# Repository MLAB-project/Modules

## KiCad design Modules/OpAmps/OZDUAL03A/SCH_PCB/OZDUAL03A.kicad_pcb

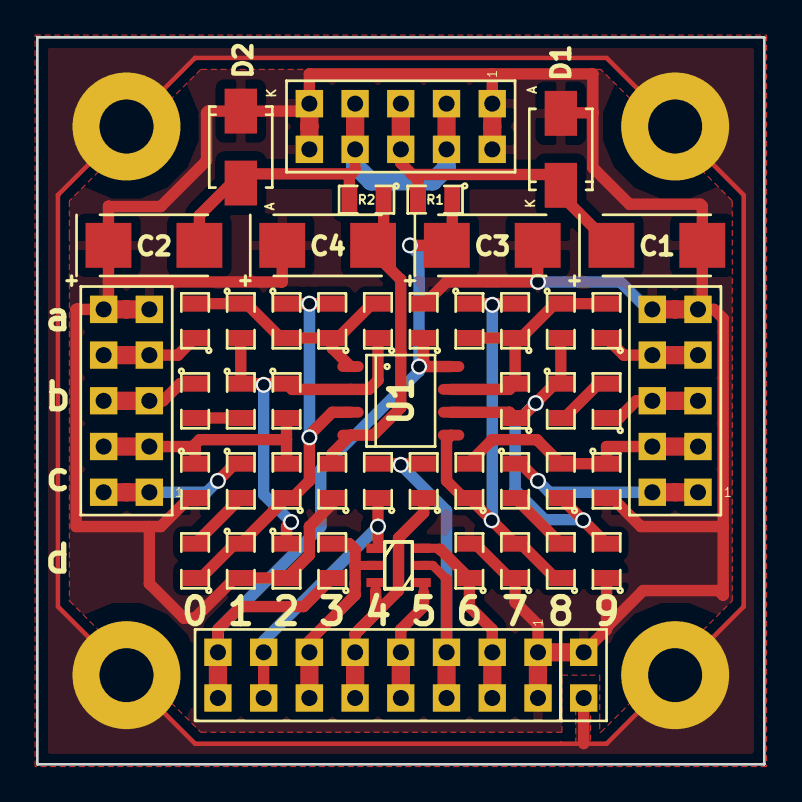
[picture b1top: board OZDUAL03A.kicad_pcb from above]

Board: 2 copper layers, 40.4 x 40.4 mm, 55 parts (0 on the bottom side), 30 nets.

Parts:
C1, C2, C3, C4: 47u; TantalC_SizeC_Reflow
D1, D2: M4; Diode-SMA_Standard
J1: JUMP2_2x1; Straight_2x01
J2: POWER; Straight_2x05
J3: OPAMPA; Straight_2x05
J4: OPAMPB; Straight_2x05
J5: SOT23-6; Straight_2x08
M1, M2, M3, M4: HOLE; MountingHole_3mm
Q1: BC846; SOT-23-3
R1, R2: R; SMD-0805
U1: OZ; SO-8
U2: MAX6066; SOT-23-3
U3: ANALOG SWITCH; SOT-23-6
a0, a2, a4, a6, a9: C; SMD-0805
a1, a3, a7, a8: R; SMD-0805
a5: 100nF; SMD-0805
b0, b7, b9: C; SMD-0805
b1, b2, b8: R; SMD-0805
c0, c1, c4, c5, c7, c9: C; SMD-0805
c2, c6, c8: R; SMD-0805
c3: 100nF; SMD-0805
d0, d1, d2, d3, d6, d7, d8, d9: R; SMD-0805

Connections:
/1: J5.13, J5.14, U2.1, U3.1, c4.1
/2: J5.11, J5.12, Q1.3, U3.2, d3.2
/3: J5.9, J5.10, U2.2, U3.3, c5.1
/4: J5.7, J5.8, Q1.1, U3.4
/5: J5.5, J5.6, U2.3, U3.5, c4.2, c5.2
/6: J5.3, J5.4, Q1.2, U3.6, d6.1
/INA+: J3.1, J3.2, c1.1
/INA-: J3.5, J3.6, b0.1
/INB+: J4.1, J4.2, c7.1
/INB-: J4.5, J4.6, b9.1
/OUTA: J3.7, J3.8, a0.1
/OUTB: J4.7, J4.8, a9.1
/VIN+: C1.1, D1.1, J2.5, J2.6, R1.2
/VIN-: C2.2, D2.2, J2.3, J2.4, J2.7, J2.8, R2.2
/VREFA: J3.3, J3.4, b2.2, c0.1, c2.2
/VREFB: J4.3, J4.4, c6.2, c8.2, c9.1
GND: J1.2, M1.1, M2.1, M3.1, M4.1
GNDA: C1.2, C2.1, C3.2, C4.1, D1.2, D2.1, J1.1, J2.1, J2.2, J2.9, J2.10, J3.9, J3.10, J4.9, J4.10, J5.1, J5.2, a5.2, c0.2, c3.1, c9.2, d1.2, d2.2, d6.2, d7.1, d9.1
unnamed: U1.1, a0.2, a1.1, a2.2, a3.1, a4.2
unnamed: U1.2, a1.2, a4.1, b1.1, b2.1, d2.1
unnamed: U1.3, a2.1, a3.2, c2.1, d0.1, d1.1
unnamed: U1.5, a6.1, a7.2, c6.1, d7.2, d8.1
unnamed: U1.6, a8.2, b7.1, b8.1, c8.1, d9.2
unnamed: U1.7, a6.2, a7.1, a8.1, a9.2, b7.2
unnamed: b0.2, b1.2
unnamed: b8.2, b9.2
unnamed: c1.2, d0.2
unnamed: c7.2, d8.2
VCC: C3.1, J5.15, J5.16, R1.1, U1.8, a5.1, d3.1
VSS: C4.2, R2.1, U1.4, c3.2

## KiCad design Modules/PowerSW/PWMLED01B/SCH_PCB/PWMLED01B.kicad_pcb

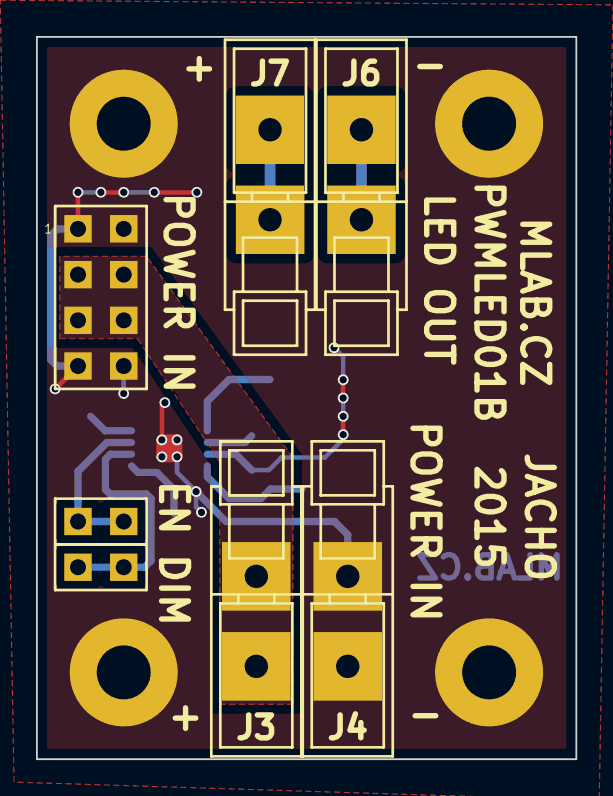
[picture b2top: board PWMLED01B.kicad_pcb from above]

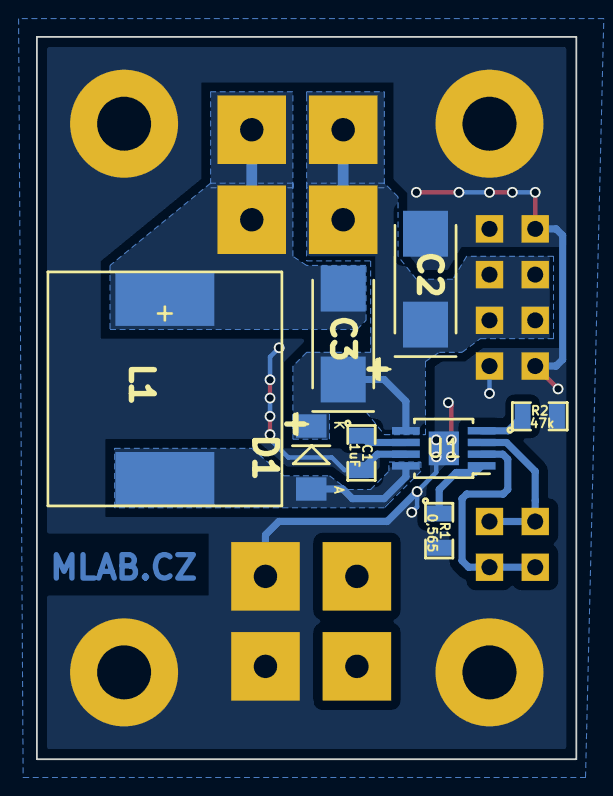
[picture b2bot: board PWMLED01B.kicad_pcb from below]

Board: 2 copper layers, 30.0 x 40.1 mm, 19 parts (8 on the bottom side), 9 nets.

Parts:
C1: 1uF; SMD-0805
C2, C3: 4,7uF; TantalC_SizeC_Reflow
D1: TMMBAT48; Diode-MiniMELF_Standard
J1, J2: JUMP_2x1; Straight_1x02
J3, J4, J6, J7: WAGO256
J5: JUMP_4X2; Straight_2x04
L1: DE1207-22 (22uH); DE1205-10
P1, P2, P3, P4: M3; MountingHole_3mm
R1: 0,565; SMD-0805
R2: 47k; SMD-0805
U1: LM3407; MSOP-8-1EP_3x3mm_Pitch0.65mm

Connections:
/+LED: C2.1, C3.1, D1.2, J3.1, J5.3, J5.4, J5.5, J5.6, J7.1, U1.5
/-LED: C3.2, J6.1, L1.1
/DIM: J1.1, J1.2, U1.2
/EN: J2.1, J2.2, U1.3
GND: C1.2, C2.2, J4.1, J5.1, J5.2, J5.7, J5.8, P1.1, P2.1, P3.1, P4.1, R1.2, R2.2, U1.7, U1.9
unnamed: C1.1, U1.6
unnamed: D1.1, L1.2, U1.8
unnamed: R1.1, U1.1
unnamed: R2.1, U1.4

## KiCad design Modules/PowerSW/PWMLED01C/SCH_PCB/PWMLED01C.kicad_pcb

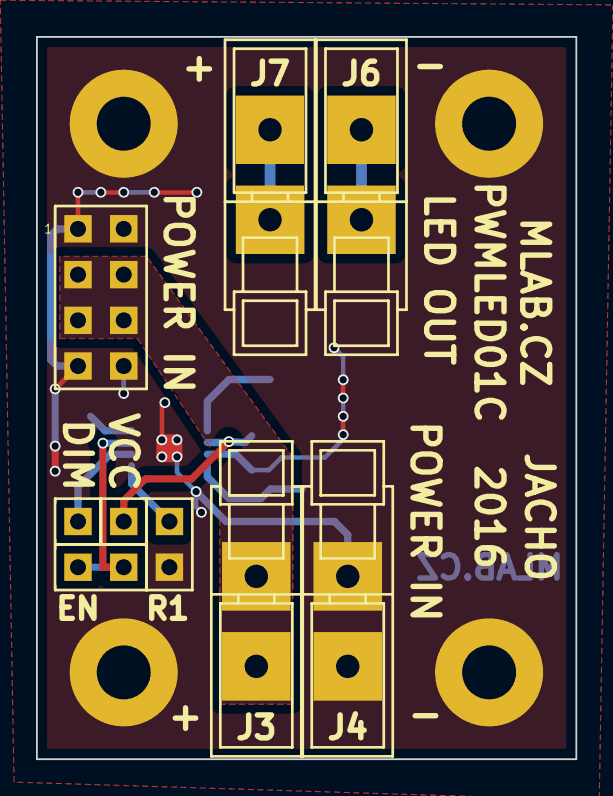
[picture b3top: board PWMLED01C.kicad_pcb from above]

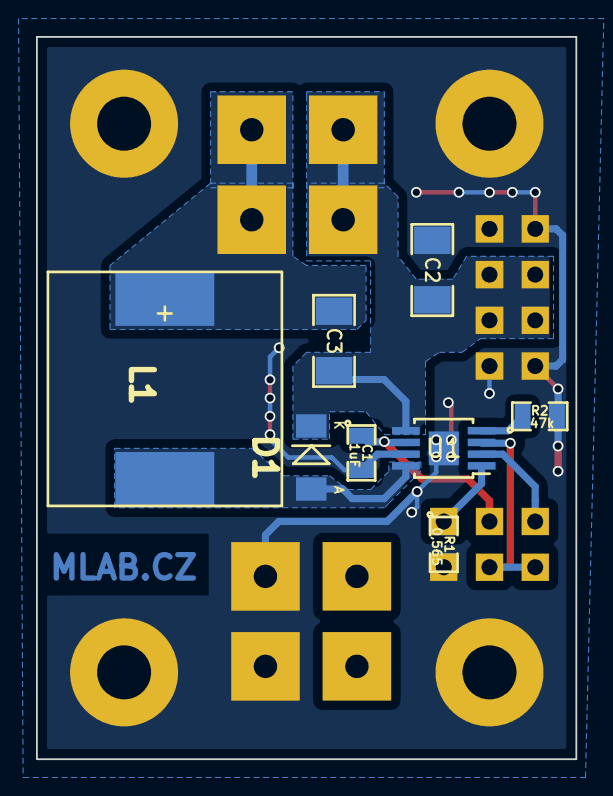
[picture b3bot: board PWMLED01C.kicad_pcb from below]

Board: 2 copper layers, 30.0 x 40.1 mm, 21 parts (8 on the bottom side), 9 nets.

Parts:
C1: 1uF; SMD-0805
C2, C3: 4,7uF/50V; SMD-1206
D1: TMMBAT48; Diode-MiniMELF_Standard
J1: CONN1_2; Straight_1x02
J2: JUMP_2x1; Straight_1x02
J3, J4, J6, J7: WAGO256
J5: JUMP_4X2; Straight_2x04
J8, J9: CONN1_1; Straight_1x01
L1: DE1207-22 (22uH); DE1205-10
P1, P2, P3, P4: M3; MountingHole_3mm
R1: 0,565; SMD-0805
R2: 47k; SMD-0805
U1: LM3407; MSOP-8-1EP_3x3mm_Pitch0.65mm

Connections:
/+LED: C2.1, C3.2, D1.2, J3.1, J5.3, J5.4, J5.5, J5.6, J7.1, U1.5
/-LED: C3.1, J6.1, L1.1
/DIM: J9.1, U1.2
/EN: J2.1, J2.2, U1.3
/Vcc: C1.1, J8.1, U1.6
GND: C1.2, C2.2, J1.1, J4.1, J5.1, J5.2, J5.7, J5.8, P1.1, P2.1, P3.1, P4.1, R1.2, R2.2, U1.7, U1.9
unnamed: D1.1, L1.2, U1.8
unnamed: J1.2, R1.1, U1.1
unnamed: R2.1, U1.4

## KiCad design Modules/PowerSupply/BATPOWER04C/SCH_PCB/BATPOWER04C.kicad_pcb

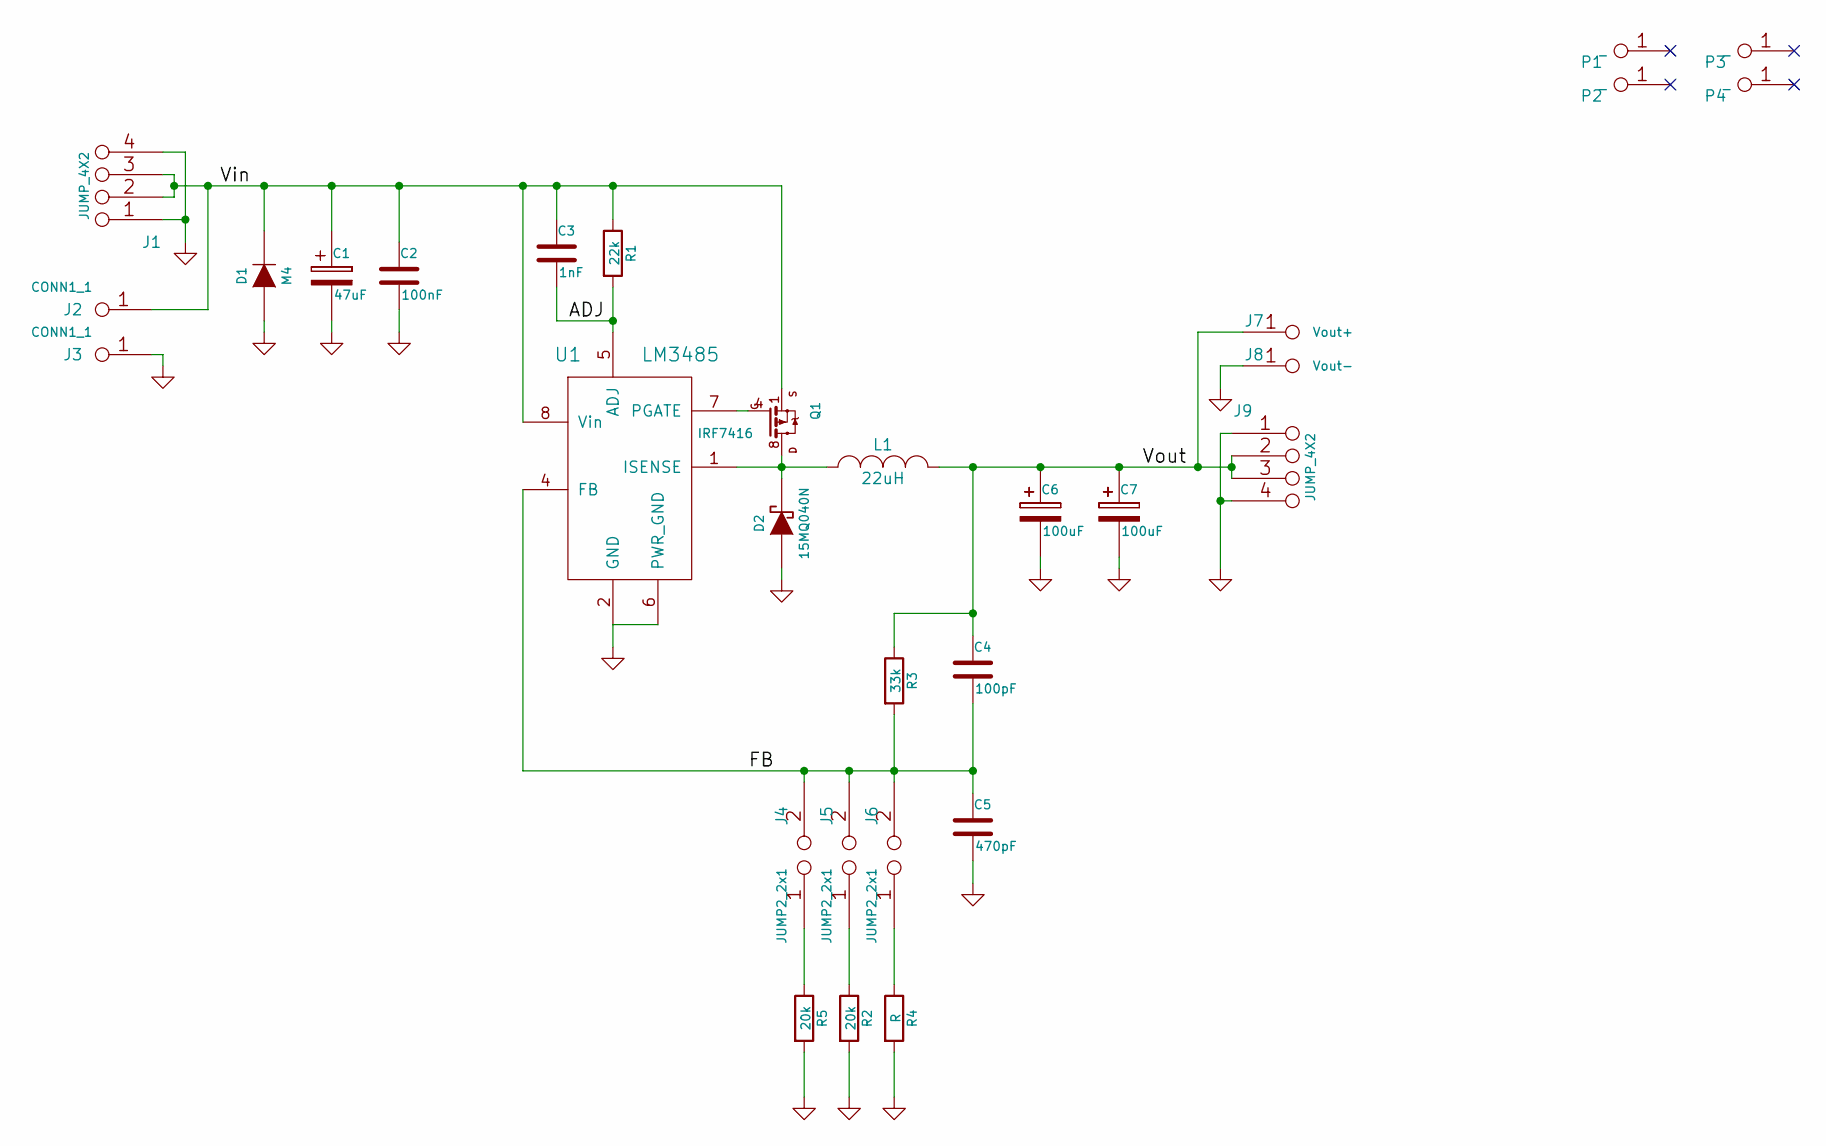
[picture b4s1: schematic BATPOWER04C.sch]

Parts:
C1: 47uF; TantalC_SizeC_Reflow
C2: 100nF; SMD-0805
C3: 1nF; SMD-0805
C4: 100pF; SMD-0805
C5: 470pF; SMD-0805
C6, C7: 100uF; TantalC_SizeD_Reflow
D1: M4; Diode-SMA_Standard
D2: 15MQ040N; Diode-SMA_Standard
J1, J9: JUMP_4X2; Pin_Header_Straight_2x04
J2, J3: CONN1_1; WAGO256
J4, J5, J6: JUMP2_2x1; Pin_Header_Straight_1x02
J7: Vout+; WAGO256
J8: Vout-; WAGO256
L1: 22uH; DE1205-10
P1, P2, P3, P4: _; MountingHole_3mm
Q1: IRF7416; SO-8
R1: 22k; SMD-0805
R2, R5: 20k; SMD-0805
R3: 33k; SMD-0805
R4: R; SMD-0805
U1: LM3485; MSOP-8_3x3mm_Pitch0.65mm

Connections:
/ADJ: C3.2, R1.2, U1.5 (ADJ)
/FB: C4.2, C5.1, J4.2, J5.2, J6.2, R3.2, U1.4 (FB)
/Vin: C1.1, C2.1, C3.1, D1.2 (K), J1.2, J1.3, J1.6, J1.7, J2.1, Q1.1 (S), Q1.2 (S), Q1.3 (S), R1.1, U1.8 (Vin)
/Vout: C4.1, C6.1, C7.1, J7.1, J9.2, J9.3, J9.6, J9.7, L1.2, R3.1
GND: C1.2, C2.2, C5.2, C6.2, C7.2, D1.1 (A), D2.1 (A), J1.1, J1.4, J1.5, J1.8, J3.1, J8.1, J9.1, J9.4, J9.5, J9.8, R2.2, R4.2, R5.2, U1.2 (GND), U1.6 (PWR_GND)
unnamed: D2.2 (K), L1.1, Q1.5 (D), Q1.6 (D), Q1.7 (D), Q1.8 (D), U1.1 (ISENSE)
unnamed: J4.1, R5.1
unnamed: J5.1, R2.1
unnamed: J6.1, R4.1
unnamed: Q1.4 (G), U1.7 (PGATE)

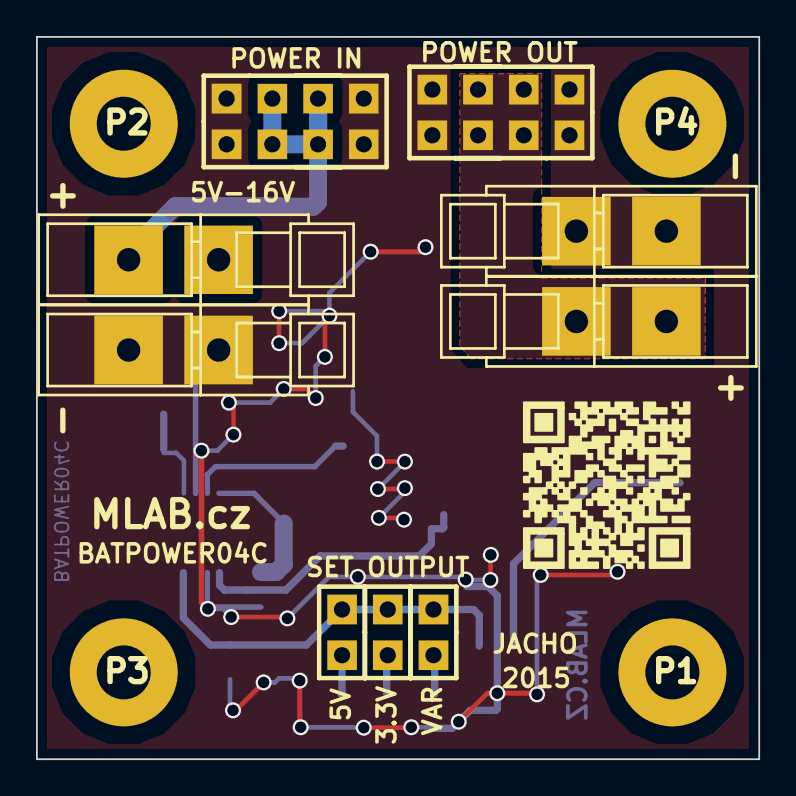
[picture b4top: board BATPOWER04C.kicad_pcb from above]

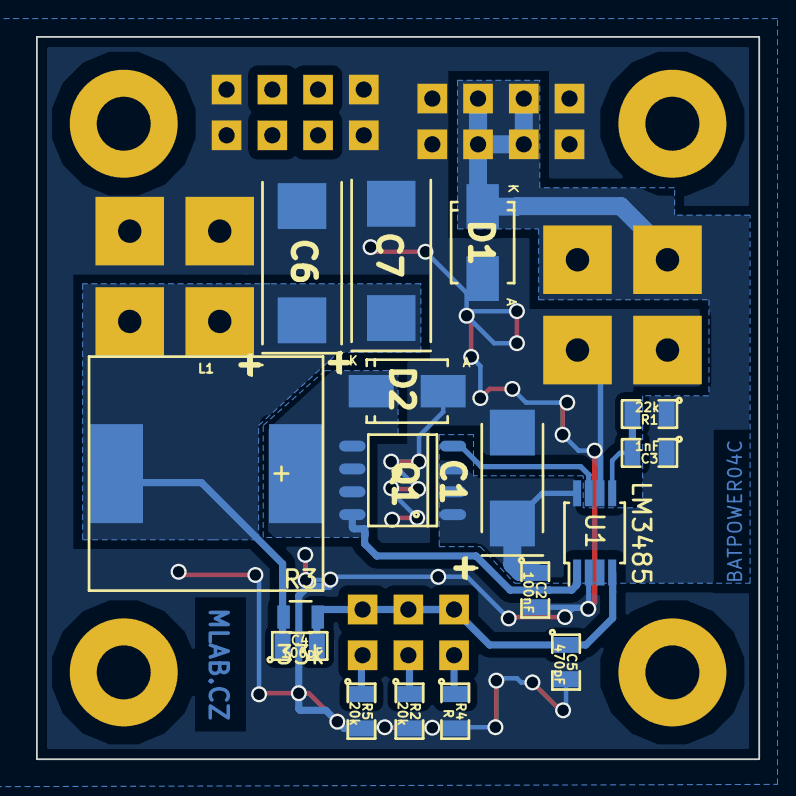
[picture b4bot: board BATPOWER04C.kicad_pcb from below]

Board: 2 copper layers, 40.1 x 40.1 mm, 30 parts (17 on the bottom side), 10 nets.

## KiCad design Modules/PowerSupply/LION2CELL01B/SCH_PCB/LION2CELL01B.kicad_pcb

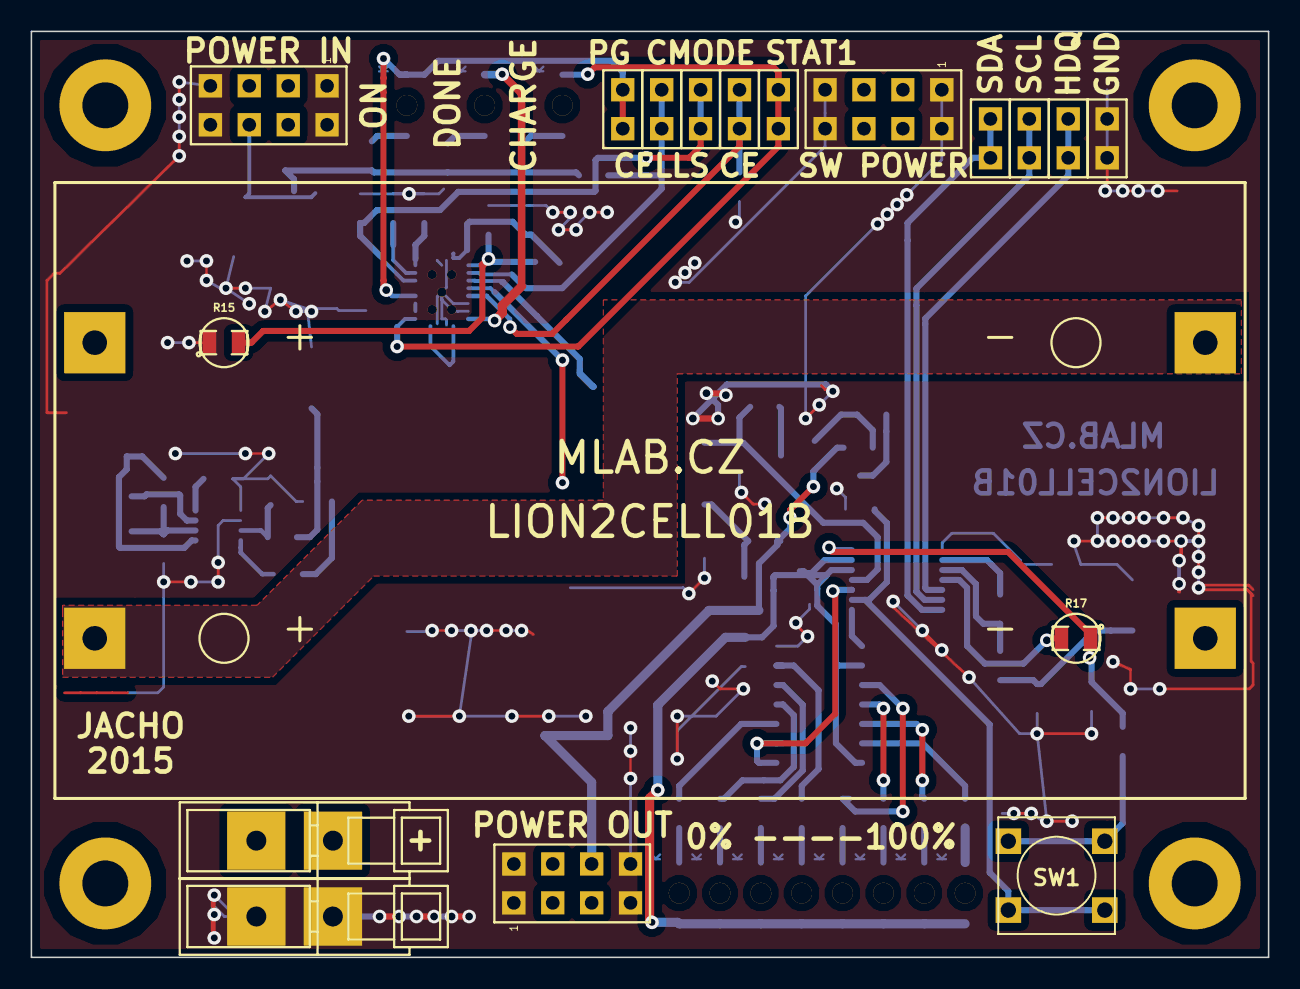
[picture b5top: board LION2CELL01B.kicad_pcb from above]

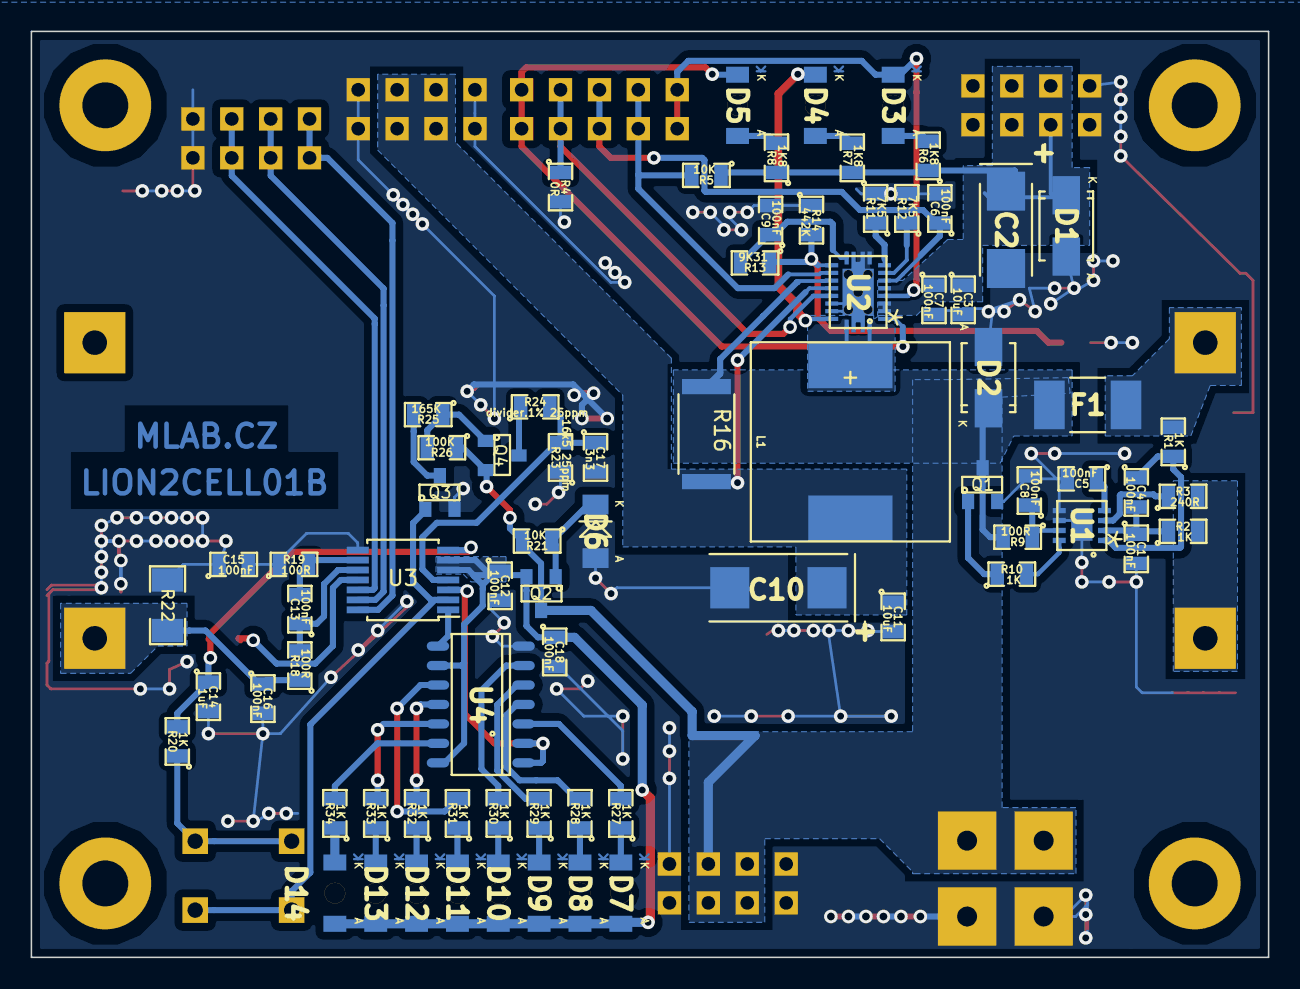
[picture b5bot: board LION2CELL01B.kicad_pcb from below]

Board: 2 copper layers, 80.8 x 60.5 mm, 96 parts (74 on the bottom side), 61 nets.

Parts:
BT1: 2x18650_LION; 2LION
C1, C4, C5, C6, C7, C8, C9, C12, C13, C15, C16, C18: 100nF; SMD-0805
C2: 47uF; TantalC_SizeC_Reflow
C3, C11: 10uF; SMD-0805
C10: 100uF; TantalC_SizeD_Reflow
C14: 1uF; SMD-0805
C17: 3n3; SMD-0805
D1, D2: M4; SMA_Standard
D3, D4, D5: LED; LED_1206
D6: BZV55C-5,6V; MiniMELF_Standard
D7, D8, D9, D10, D11, D12, D13, D14: ORAGE; LED_1206
F1: FUSE; 2410
J1, J7, J13: JUMP_4X2; Straight_2x04
J2, J3, J4, J5, J6, J10, J11, J12, J14: JUMP_2x1; Straight_1x02
J8, J9: CONN1_1; WAGO256
L1: DE1205-10
P1, P2, P3, P4: _; MountingHole_3mm
Q1: IRLML6244; SOT-23
Q2, Q3: MMBF170LT1G; SOT-23
Q4: BSS83P; SOT-23
R1, R2, R10, R20, R27, R28, R29, R30, R31, R32, R33, R34: 1K; SMD-0805
R3: 240R; SMD-0805
R4: 0R; SMD-0805
R5, R21: 10K; SMD-0805
R6, R7, R8: 1K8; SMD-0805
R9, R18, R19: 100R; SMD-0805
R11, R12: 7K5; SMD-0805
R13: 9K31; SMD-0805
R14: 442K; SMD-0805
R15: NCP21XV103J03RA; SMD-0805
R16: 0R1; R_2512
R17: 10K NTC; SMD-0805
R22: 0R01 75PPM; SMD-1206
R23: 16k5 25ppm; SMD-0805
R24: divider.1% 25ppm; SMD-0805
R25: 165K; SMD-0805
R26: 100K; SMD-0805
SW1: SW_PUSH; SW_PUSH_SMALL
U1: BQ29209; VSON-8
U2: BQ24103; VQFN-20
U3: BQ34Z100; TSSOP-14_4.4x5mm_Pitch0.65mm
U4: SN74HC164D; SO-14

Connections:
/BAT+: BT1.1, F1.1, R1.2
/BAT-MIDPOINT: BT1.3, R2.2, R3.2
/BATTERY+: D2.2, F1.2, J7.3, J7.4, J7.5, J7.6, J8.1, Q1.D, Q2.D, Q4.S, R9.2, R16.1, R21.2, R26.1, U2.14
/BATTERY-: BT1.4, C16.1, R18.1, R22.1
/CE: J5.1, J5.2, R4.1, U2.16
/CELLS: J6.1, J6.2, R5.2, U2.13
/CMODE: C6.1, J4.1, J4.2, U2.7
/HDQ: J12.1, J12.2, U3.12
/P1: U3.3, U4.1, U4.2
/P2: U3.1, U4.8
/PG: D3.2, J3.1, J3.2, U2.5
/REGIN: C12.1, C18.1, D7.1, D8.1, D9.1, D10.1, D11.1, D12.1, D13.1, D14.1, Q2.S, U3.5, U3.6, U4.9, U4.14
/SCL: J11.1, J11.2, U3.13
/SDA: J10.1, J10.2, U3.14
/STAT1: D5.2, J2.1, J2.2, U2.2
GND: C1.2, C2.2, C3.2, C5.2, C6.2, C7.2, C8.2, C9.2, C10.2, C11.2, C12.2, C14.2, C15.1, C15.2, C16.2, C17.2, C18.2, D1.1, D2.1, D6.1, J1.1, J1.2, J1.7, J1.8, J7.1, J7.2, J7.7, J7.8, J9.1, J13.1, J13.2, J13.7, J13.8, J14.1, J14.2, Q1.S, Q3.S, R4.2, R11.2, R12.2, R14.1, R15.1, R19.1, R22.2, R23.1, U1.5, U1.6, U1.9, U2.10, U2.17, U2.18, U2.21, U3.8, U4.7
unnamed: C1.1, C4.2, R2.1, U1.2
unnamed: C2.1, C3.1, C7.1, D1.2, J1.3, J1.4, J1.5, J1.6, R5.1, R6.1, R7.1, R8.1, U2.3, U2.4, U2.6
unnamed: C4.1, R1.1, U1.1
unnamed: C5.1, U1.4
unnamed: C8.1, R9.1, U1.7
unnamed: C9.1, R13.2, U2.11
unnamed: C10.1, C11.1, J13.3, J13.4, J13.5, J13.6, L1.2, R16.2, U2.15
unnamed: C13.1, R18.2, U3.10
unnamed: C13.2, R19.2, U3.9
unnamed: C14.1, R17.1, R20.2, U3.7
unnamed: C17.1, R23.2, R24.2, U3.4
unnamed: D3.1, R6.2
unnamed: D4.1, R7.2
unnamed: D4.2, U2.19
unnamed: D5.1, R8.2
unnamed: D6.2, Q2.G, R21.1
unnamed: D7.2, R27.1
unnamed: D8.2, R28.1
unnamed: D9.2, R29.1
unnamed: D10.2, R30.1
unnamed: D11.2, R31.1
unnamed: D12.2, R32.1
unnamed: D13.2, R33.1
unnamed: D14.2, R34.1
unnamed: L1.1, U2.1, U2.20
unnamed: Q1.G, R10.1
unnamed: Q3.D, R25.2
unnamed: Q3.G, SW1.2, U3.2
unnamed: Q4.D, R24.1
unnamed: Q4.G, R25.1, R26.2
unnamed: R3.1, U1.3
unnamed: R10.2, U1.8
unnamed: R11.1, U2.9
unnamed: R12.1, U2.8
unnamed: R13.1, R14.2, R15.2, U2.12
unnamed: R17.2, U3.11
unnamed: R20.1, SW1.1
unnamed: R27.2, U4.3
unnamed: R28.2, U4.4
unnamed: R29.2, U4.5
unnamed: R30.2, U4.6
unnamed: R31.2, U4.10
unnamed: R32.2, U4.11
unnamed: R33.2, U4.12
unnamed: R34.2, U4.13

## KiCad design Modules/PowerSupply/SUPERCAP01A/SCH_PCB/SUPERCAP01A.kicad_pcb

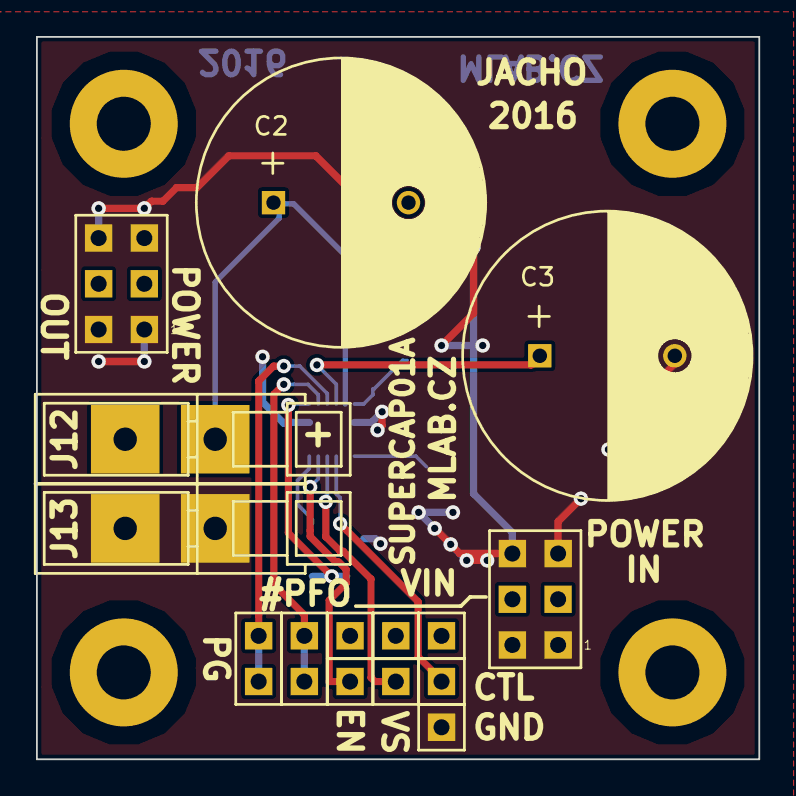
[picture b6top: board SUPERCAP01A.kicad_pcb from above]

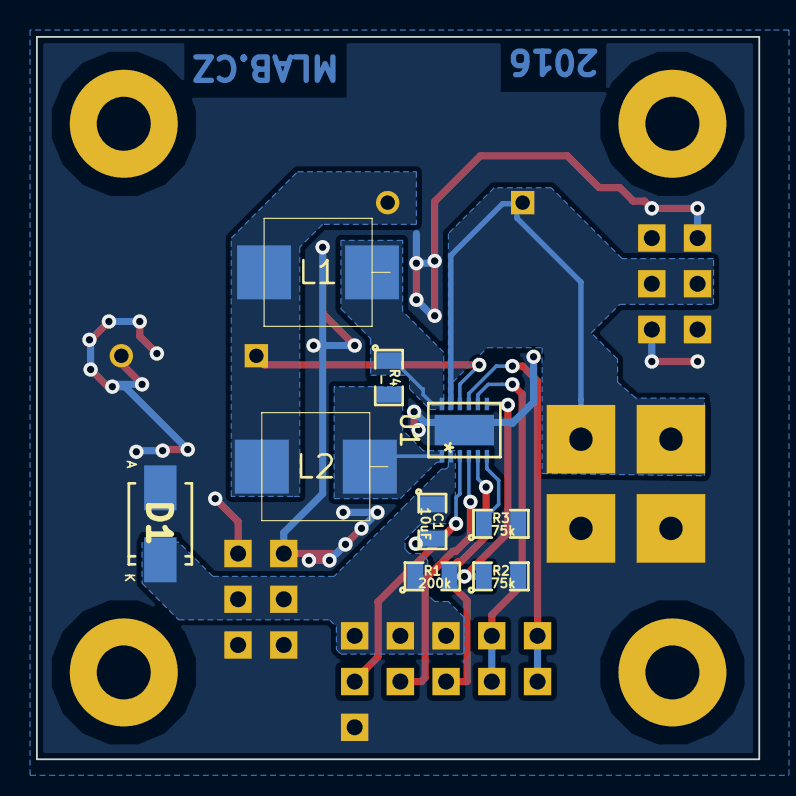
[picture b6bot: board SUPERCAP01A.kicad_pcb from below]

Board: 2 copper layers, 40.1 x 40.1 mm, 28 parts (9 on the bottom side), 13 nets.

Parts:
C1: 10uF; SMD-0805
C2, C3: 22F; C_Radial_D16_L25_P7.5
D1: M4; SMA_Standard
J1, J11: JUMP_3X2; Straight_2x03
J2, J3, J4, J5, J6, J7, J8: CONN1_1; Straight_1x01
J9, J10: JUMP_2x1; Straight_2x01
J12, J13: CONN1_1; WAGO256
L1, L2: DER0705-3.3uH; DER0705
M1, M2, M3, M4: HOLE; MountingHole_3mm
R1: 200k; SMD-0805
R2, R3: 75k; SMD-0805
R4: -; SMD-0805
U1: LTC3625; DFN-12-1EP_3x4mm_Pitch0.5mm

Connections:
/#PFO: J9.1, J9.2, U1.8
/CTL: J3.1, U1.3
/EN: J6.1, U1.5
/PG: J10.1, J10.2, U1.9
/VIN: C1.1, D1.2, J1.3, J1.4, J2.1, J5.1, J7.1, R1.1, U1.2
/VSEL: J8.1, U1.4
GND: C1.2, C3.2, D1.1, J1.1, J1.2, J1.5, J1.6, J4.1, J11.1, J11.2, J11.5, J11.6, J13.1, R2.2, R3.2, U1.13
unnamed: C2.1, J11.3, J11.4, J12.1, U1.11
unnamed: C2.2, C3.1, L1.2, L2.2, U1.10
unnamed: L1.1, R4.1, U1.12
unnamed: L2.1, R4.2, U1.1
unnamed: R1.2, R2.1, U1.7
unnamed: R3.1, U1.6
